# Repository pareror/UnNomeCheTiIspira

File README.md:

# 🏙️ NoisTOp / Torino Noise Monitor

<div align="center">

**Rete urbana di sensori acustici intelligenti per la gestione preventiva della movida e la sicurezza stradale.**

[Panoramica](#-visione-del-progetto) • [Come Funziona](#-come-funziona) • [Edge AI](#-edge-ai--machine-learning) • [Hardware & BOM](#-hardware-prototipo-vs-produzione-reale-10-) • [Sicurezza](#-architettura--politiche-di-sicurezza) • [Comandi & Setup](#-avvio-rapido)

</div>

---

## 🎯 Visione del Progetto

Le aree urbane ad alta densità di vita notturna (es. San Salvario, Vanchiglia e Centro a Torino) affrontano quotidianamente due sfide parallele:

| 🔇 Gestione Rumore Urbano | 🚨 Sicurezza Stradale Notturna |
|---|---|
| **Problema:** Conflitto costante tra locali (rischio sanzioni e chiusura) e residenti (diritto al riposo). I controlli tradizionali sono lenti, punitivi ed *ex-post*. | **Problema:** Eventi critici (urla di aiuto, spari, schianti o incidenti) rischiano di non essere segnalati tempestivamente alle forze dell'ordine. |
| **Soluzione NoiStop:** Monitoraggio continuo in dB(A), segnalazione visiva (LED) in loco e **allerta preventiva via Telegram** all'esercente per consentirgli di abbassare il volume prima dell'arrivo delle multe. | **Soluzione NoiStop:** Riconoscimento istantaneo on-device dei suoni di emergenza tramite TinyML con **notifica immediata alle Forze dell'Ordine** e localizzazione precisa. |

> [!NOTE]
> **🛡️ Zero Audio Storage & Piena Conformità GDPR**  
> L'elaborazione del segnale avviene **interamente on-edge**: i campioni audio risiedono solo per poche frazioni di secondo nella RAM volatile del sensore per il calcolo dei dB e della classe, e vengono **immediatamente distrutti**. Nessuna registrazione vocale o audio viene salvata su disco né trasmessa via rete, garantendo la totale assenza di dati personali.

---

## ⚡ Come Funziona

Il sistema opera su tre percorsi paralleli ad alta efficienza:

```mermaid
flowchart LR
    MIC["🎙️ Mic 16 kHz"] --> DSP["⚡ Front-End DSP (Log-Mel)"]
    
    %% Canale 1: Telemetria & LED
    DSP -->|RMS dBFS| SPL["📊 Calibrazione dB SPL"]
    SPL -->|Locale| LED["🚦 LED Tricolore\n(Verde / Giallo / Rosso)"]
    SPL -->|1 Hz HTTP| SRV["🖥️ Master Server (Next.js)"]
    
    %% Canale 2: Persistenza
    SRV --> DB[("💾 SQLite WAL")]
    DB --> PERS{"⏱️ Persistente?\n>10 min & ≥70 dB"}
    PERS -->|Sì + Locale Aperto| TEL_BAR["📱 Alert Telegram Esercente\n(raggio 150m)"]
    
    %% Canale 3: Safety AI
    DSP -->|TinyML INT8| AI{"🤖 DS-CNN Classifier"}
    AI -->|Urla / Spari > 80%| OLED["📟 OLED Display\n'SCREAM 93%'"]
    AI -->|Allerta Immediata| POLICE["🚨 Notifica Forze dell'Ordine\n(Tutta la Città)"]
    
    %% Mappa Web
    SRV -->|SSE 0ms| MAP["🗺️ Live Heatmap Web (Torino)"]
```

### 1. Indicatore Visivo Immediato (Autodisciplina)
Un modulo LED posto all'esterno del locale restituisce il livello acustico in tempo reale:
* 🟢 **Verde (< 66 dB):** Livello ottimale / nominale.
* 🟡 **Giallo (66 – 80 dB):** Attenzione, rumore in aumento.
* 🔴 **Rosso (≥ 81 dB o Pericolo):** Superamento soglia o evento critico rilevato.

### 2. Allerta Preventiva ad Escalation (Regola dei 10 Minuti)
* **Condizione:** Rumore continuo $\ge 70\text{ dB}$ per almeno **10 minuti**.
* **Filtro Orari Intelligente:** Tramite OpenStreetMap / Google Places, il sistema verifica se il locale è effettivamente aperto.
* **Anti-Spam:** Cooldown minimo di 10 minuti tra avvisi consecutivi allo stesso locale.
* **Escalation:** Se l'anomalia persiste dopo l'avviso preventivo, l'infrazione viene registrata per i report formali delle autorità.

### 3. Canale di Emergenza Sicurezza (Safety Path)
Se il classificatore TinyML riconosce suoni di pericolo (`scream`, `gunshot`, `siren`, `impact_crash`) con **confidenza > 80%**:
1. Mostra l'evento sul display OLED locale per 10 secondi.
2. Invia all'istante l'allerta con coordinate ai canali della **Polizia Locale / Forze dell'Ordine** (senza vincoli di raggio).

---

## 🧠 Edge AI & Machine Learning

Il classificatore è ottimizzato per microcontrollori a bassissimo consumo e costo ridotto:

* **Architettura:** **DS-CNN** (*Depthwise Separable Convolutional Neural Network*), conforme agli standard MLPerf Tiny.
* **Quantizzazione:** **INT8** completo (footprint **< 100 KB** in memoria SRAM).
* **Elaborazione Audio:** Campionamento 16 kHz mono $\to$ Filtro Passa-Alto a 100 Hz (elimina rumble e vento) $\to$ Spettrogramma Log-Mel (40 bande $\times$ 49 frame per finestra da 1 s).

```
┌────────────────────────────┬────────────────────────────────────────────────────────┐
│ Categoria                  │ Classi Supportate                                      │
├────────────────────────────┼────────────────────────────────────────────────────────┤
│ 🚨 Sicurezza Urbana        │ scream (urla), gunshot (spari), impact_crash, siren    │
│ 🏙️ Rumore & Vita Notturna │ human_voice / shouting, music, engine / traffic, dog   │
│ 🍃 Fondo & Ambiente        │ ambient_quiet, silence                                 │
└────────────────────────────┴────────────────────────────────────────────────────────┘
```

> [!TIP]
> **Novelty Baseline Unsupervised:** Oltre alla classificazione, il nodo calcola le statistiche mobili (*RollingStats*) sull'embedding a 64 dimensioni per rilevare anomalie contestuali rispetto al normale profilo acustico della via.

---

## 🛠️ Hardware: Prototipo vs Produzione Reale (≤ 10 €)

### 🔬 Setup di Sviluppo & Prototipazione
Durante la fase di test e validazione è stato utilizzato:
* **Arduino UNO Q (4GB RAM):** Architettura eterogenea con **Qualcomm QRB2210** (Debian Linux, elaborazione Python + ONNX) e coprocessore **STM32U585** (pilotaggio LED deterministico e display OLED I2C SSD1306 via *RouterBridge RPC*).
* **Audio:** Microfoni USB / Jack con calibrazione dB SPL (+100 dB offset software).

---

### 🏭 Nodo Industriale di Produzione: NoiStop PCB (≤ 10 €)
Per la distribuzione in serie su pali della luce o facciate urbane è stato progettato un circuito dedicato in KiCad ([HW/NoiStop](file:///c:/Users/ale3d/Documents/VSCODE_DIRECTORY/UnNomeCheTiIspira/HW/NoiStop)):

<div align="center">

| Componente | Modello / Specifica | Funzione | Costo Est. (1000 pz) |
|---|---|---|:---:|
| **Microcontrollore (MCU)** | Espressif ESP32-WROOM-32E (8MB) | DSP, Inferenza INT8, Wi-Fi / Mesh | **2.30 €** |
| **Microfono Digitale** | TDK InvenSense MMICT5848-00-012 | MEMS digitale I2S per esterni | **1.70 €** |
| **Alimentatore AC-DC** | Hi-Link HLK-PM01 (220V ➔ 5V 3W) | Connessione diretta ai lampioni pubblici | **2.30 €** |
| **Circuito Stampato (PCB)** | Custom PCB 2-Layer KiCad | Scheda compatta a 2 layer con fori | **0.60 €** |
| **Assemblaggio (PCBA)** | SMT Pick & Place automatizzato | Saldatura industriale componenti | **0.65 €** |
| **Case Esterno** | Scatola plastica ABS Grado **IP65** | Impermeabilità e protezione UV | **1.85 €** |
| **COSTO TOTALE UNITARIO** | | *(Comprensivo di spedizione media)* | **~ 9.40 € (Max 10 €)** |

</div>

> [!IMPORTANT]
> Con un costo unitario inferiore a **10 €**, un'intera rete di 100 nodi a copertura di un quartiere richiede meno di **1.000 € di hardware**.

---

## 🔒 Architettura & Politiche di Sicurezza

Il backend adotta una strategia di hardening allineata agli standard OWASP:

```
┌─────────────────────────────────┬────────────────────────────────────────────────────────┐
│ Ambito                          │ Misura di Protezione                                  │
├─────────────────────────────────┼────────────────────────────────────────────────────────┤
│ 🛡️ Autenticazione Sensori       │ Validazione via header x-api-key o Bearer token        │
│ ⏱️ Rate Limiting Anti-DoS       │ Finestra scorrevole in RAM (max 25 req/5s per sensore) │
│ 🔐 Password Admin               │ Hash Scrypt con salt a 16 byte e timingSafeEqual       │
│ 🎫 Sessioni Web                 │ Token firmati crittograficamente con HMAC-SHA256       │
│ 👥 Ruoli Utente (RBAC)          │ Superadmin (controllo totale) vs Operatore (gestione)  │
│ 🔑 Chiavi Telegram Monouso      │ Formato TN-XXXX con indirizzo certificato pre-abbinato │
│ ⏱️ Anti-Replay Timestamp        │ Dati con età > 120 secondi scartati automaticamente    │
└─────────────────────────────────┴────────────────────────────────────────────────────────┘
```

---

## 🤖 Interfaccia Telegram (@NoiseTurin_bot)

Il bot gestisce le comunicazioni con gli esercenti e le forze dell'ordine:

| Comando | Descrizione |
|---|---|
| `/login <chiave>` | Attiva la **chiave monouso** (es. `TN-9A4B-7C2E-1D8F`). La sede e le coordinate vengono associate all'istante! |
| `/stazioni` | Elenca le celle acustiche attive entro il raggio della propria attività con distanza esatta in metri. |
| `/raggio <metri>` | Configura il raggio di pertinenza attorno alla propria sede (default: `150m`). |
| `/stato` | Riepiloga sede certificata, coordinate, raggio e orario ultimo avviso. |
| `/test_allerta` | Simula una notifica di prova per verificare la ricezione. |

---

## 🚀 Avvio Rapido

<details>
<summary><b>1. Configurazione Ambiente & Dipendenze (Clicca per espandere)</b></summary>

```bash
# Clona il repository
git clone https://github.com/pareror/UnNomeCheTiIspira.git
cd UnNomeCheTiIspira

# Installa le dipendenze
npm install

# Configura le variabili d'ambiente
cp .env.example .env.local
```

Configura `.env.local` con:
```env
TELEGRAM_BOT_TOKEN="il-tuo-bot-token"
SENSOR_API_KEY="arduino-torino-noise-secret-2026"
INITIAL_SUPERADMIN_PASSWORD="TuaPasswordSicura2026!"
```
</details>

<details>
<summary><b>2. Comandi Principali di Esecuzione</b></summary>

```bash
# Terminale 1: Server Master Full-Stack Next.js (Dashboard + API + SSE)
npm run dev

# Terminale 2: Daemon Bot Telegram
npm run bot

# Terminale 3: Simulatore stazioni di Torino (test senza hardware)
npm run simulate

# Terminale 4: Tunnel pubblico HTTPS per ricevere dati dall'esterno
npm run tunnel
```
</details>

<details>
<summary><b>3. Avvio Client su Arduino Uno Q (4GB)</b></summary>

```bash
# Esecuzione standard Python
python3 scripts/arduino_uno_q_telemetry.py --server http://192.168.22.103:3000/api/telemetry/reading

# Con stack completo Edge AI e coprocessore STM32
cd SoundObserver
python3 python/main.py
```
</details>

<details>
<summary><b>4. Sintesi Endpoint API</b></summary>

* `POST /api/telemetry/reading`: Ingestion telemetria acustica (`station_id`, `sound_intensity`, `timestamp`).
* `POST /api/alerts/safety`: Endpoint protetto per eventi di pericolo (`scream`, `gunshot`, `confidence > 0.80`).
* `GET /api/telemetry/stream?filter=all`: Streaming Server-Sent Events (SSE) a 0ms verso la dashboard.
* `GET /api/stations`: Snapshot stazioni e zone di Torino.
</details>

---

## 📄 Licenza

Distribuito sotto licenza **MIT**. Consulta il file `LICENSE` per maggiori informazioni.

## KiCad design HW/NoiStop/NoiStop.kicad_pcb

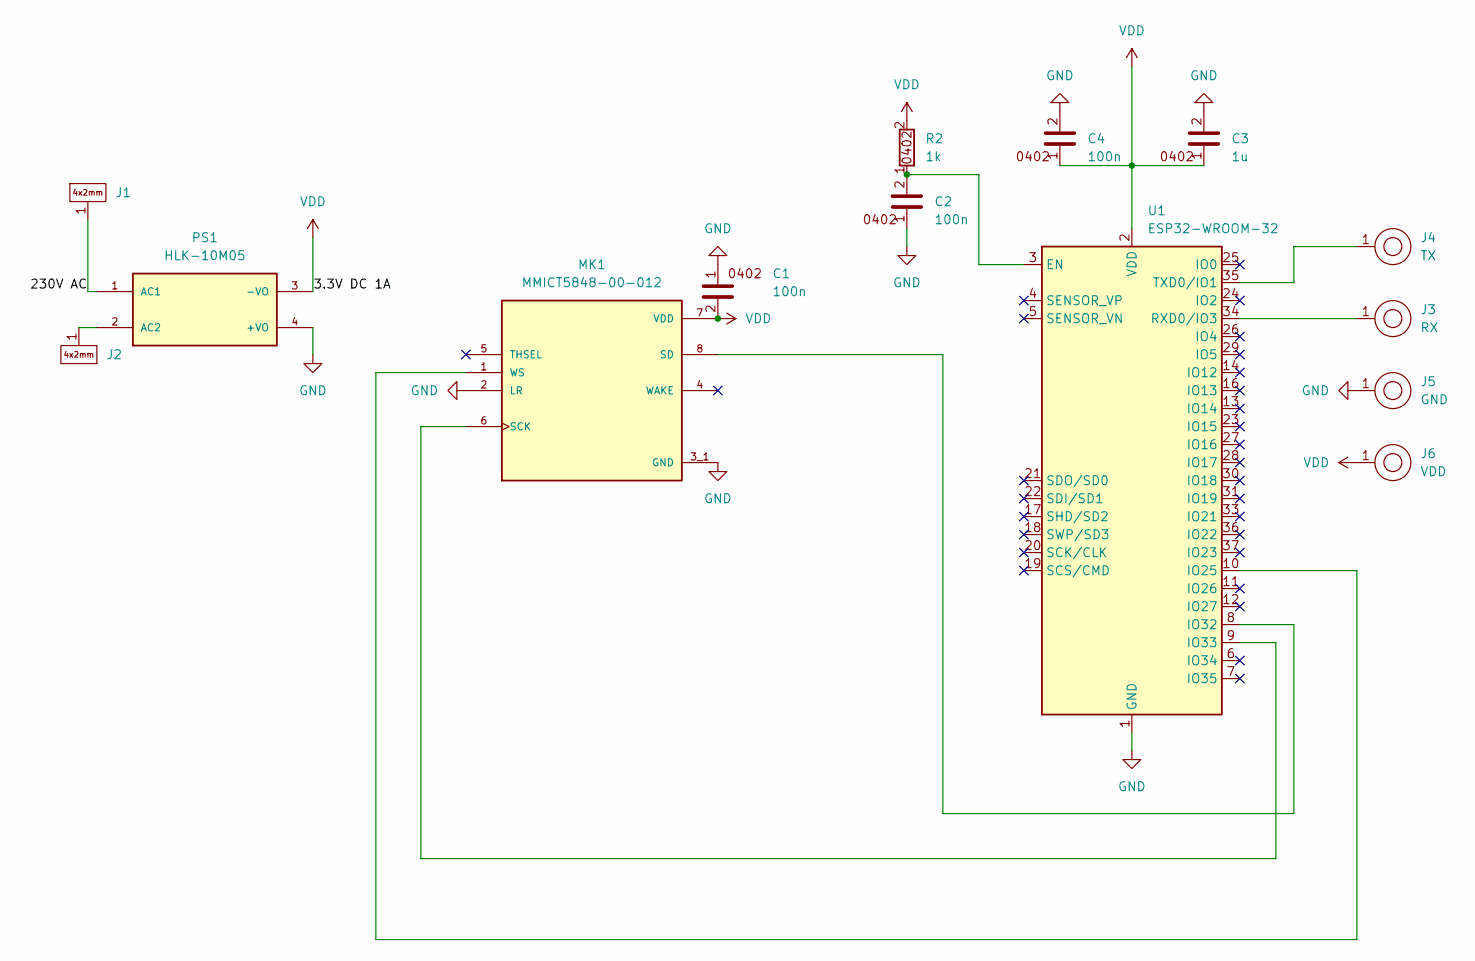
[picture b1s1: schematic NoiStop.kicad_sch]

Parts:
C1, C2, C4: 100n; C_0402_1005Metric
C3: 1u; C_0402_1005Metric
J1, J2: RECT_PAD_4X2
J3: RX; CIRC_PAD_0.7x0.3
J4: TX; CIRC_PAD_0.7x0.3
J5: GND; CIRC_PAD_0.7x0.3
J6: VDD; CIRC_PAD_0.7x0.3
MK1: MMICT5848-00-012; MIC_MMICT5848-00-012; PARTREV 1.0; DigiKey_Part_Number 1428-MMICT5848-00-012CT-ND
PS1: HLK-10M05; CONV_HLK-10M05; PARTREV V1.8
R2: 1k; R_0402_1005Metric
U1: ESP32-WROOM-32

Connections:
/230V AC: J1.1, PS1.1 (AC1)
GND: C1.1, C2.1, C3.2, C4.2, J5.1, MK1.2 (LR), MK1.3_1 (GND), MK1.3_2 (GND), PS1.4 (+VO), U1.1 (GND), U1.15 (GND), U1.38 (GND), U1.39 (GND)
unnamed: MK1.6 (SCK), U1.9 (IO33)
unnamed: MK1.8 (SD), U1.8 (IO32)
unnamed: MK1.1 (WS), U1.10 (IO25)
unnamed: J2.1, PS1.2 (AC2)
unnamed: C2.2, R2.1, U1.3 (EN)
unnamed: J3.1, U1.34 (RXD0/IO3)
unnamed: J4.1, U1.35 (TXD0/IO1)
VDD: C1.2, C3.1, C4.1, J6.1, MK1.7 (VDD), PS1.3 (-VO), R2.2, U1.2 (VDD)

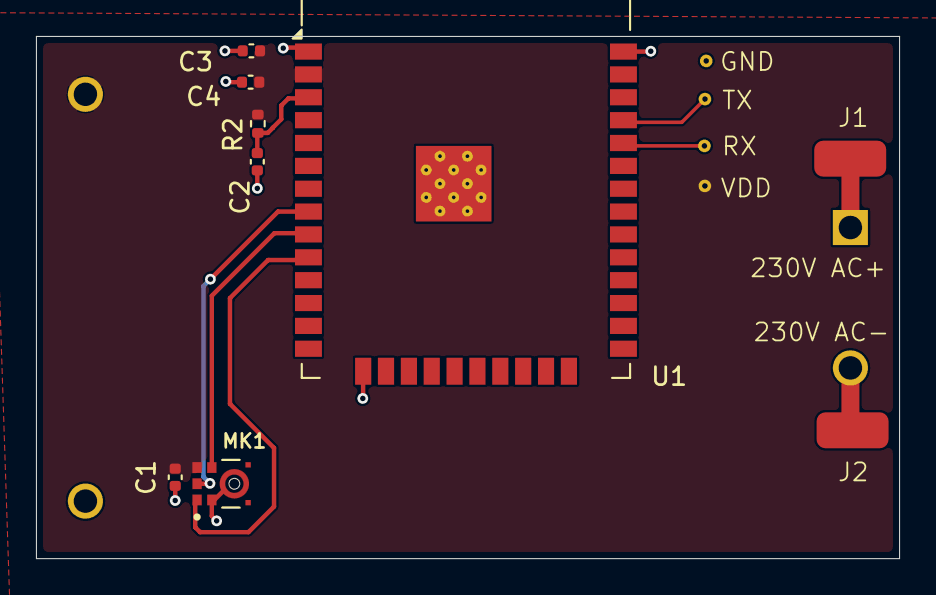
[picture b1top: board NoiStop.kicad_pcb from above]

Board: 2 copper layers, 48.0 x 29.0 mm, 14 parts (1 on the bottom side), 10 nets.

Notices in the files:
README.md:
License: MIT
